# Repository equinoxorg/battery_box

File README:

#Battery Box 2013 Prototype

##Hardware
Hardware designs are made in eagle v6

##Software
Software is MPLAB IDE X v1.30 with the Hi Tech C Lite compiler

##Changes from 2012
Added Current Sense to prevent overcurrent failure
Changed uControoler to add no volatile memory
	Can be used to prevent over discharge and better batt level estimation
	Can be used as very simple datalogger, data can be exported through Serial Data out pins
Connectors have been added to board to reduce assembely time
Surface mount components used to reduce manufacture cost

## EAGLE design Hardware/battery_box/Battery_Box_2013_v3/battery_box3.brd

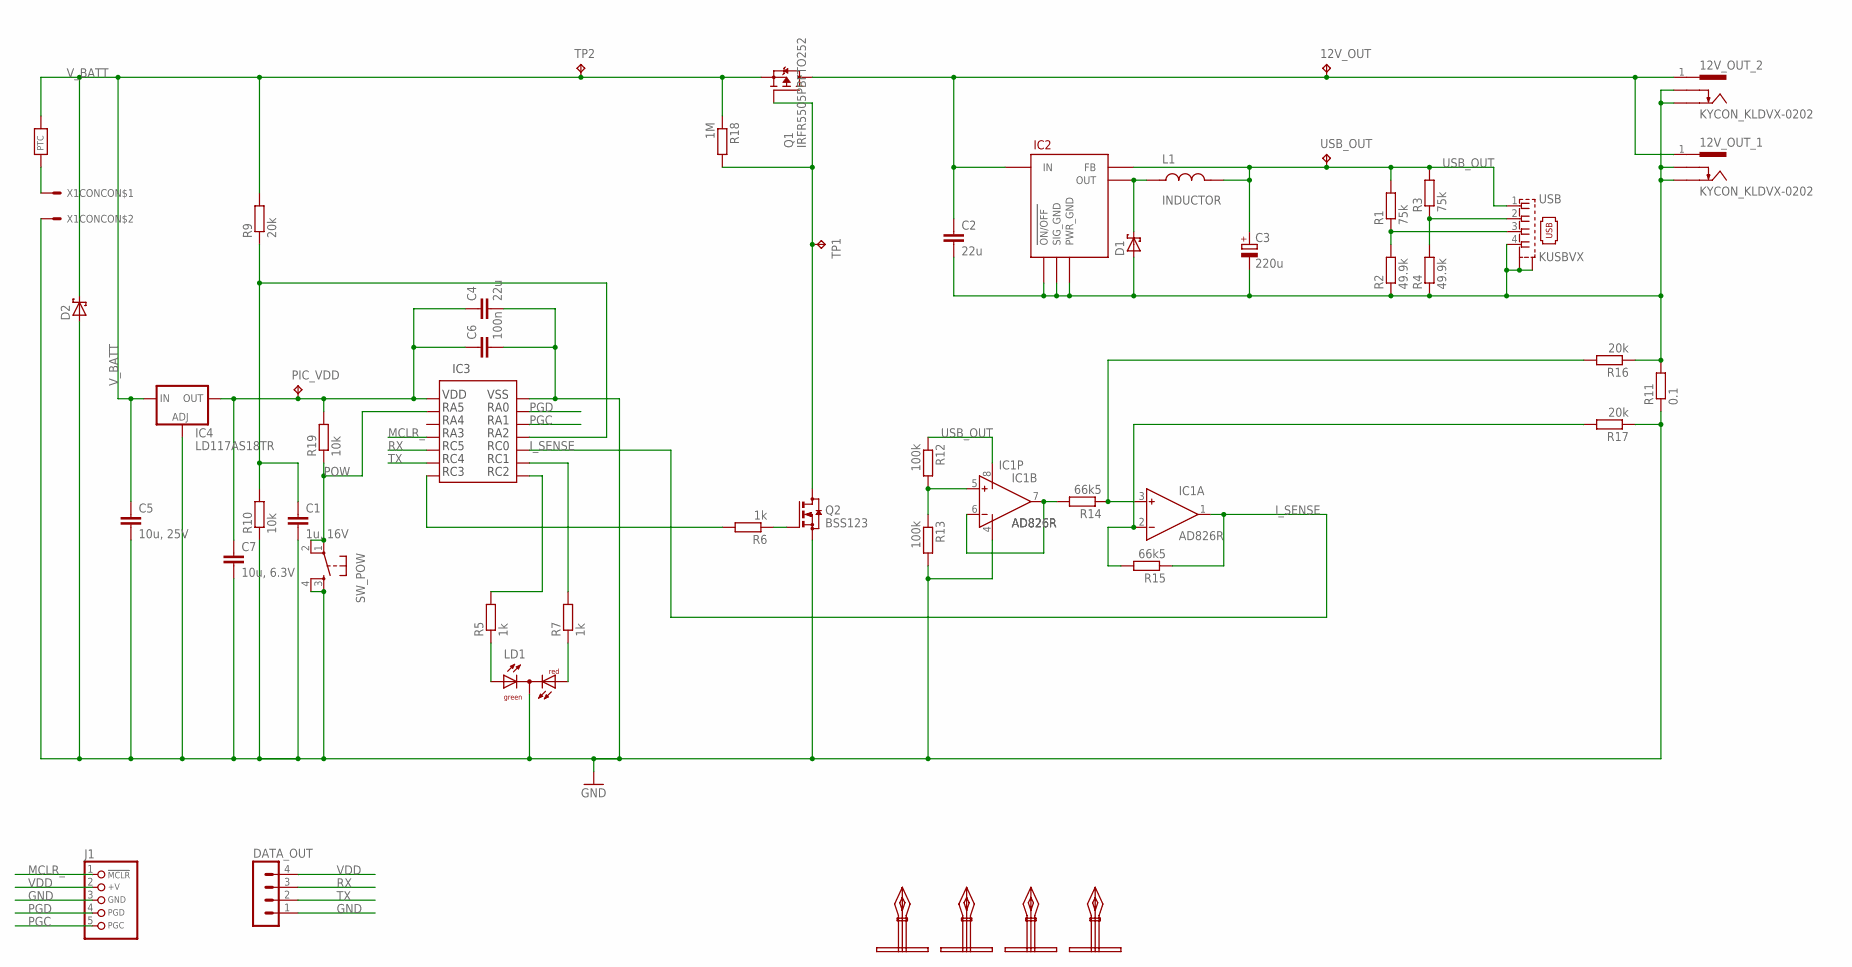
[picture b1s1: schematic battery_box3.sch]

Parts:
12V_OUT: TPTP20R; TP20R
12V_OUT_1, 12V_OUT_2: KYCON_KLDVX-0202; KYCON_KLVDX_2020_B
C1: 1u, 16V; C0805
C2: 22u; C1210
C3: 220u; PANASONIC_E
C4: 22u; C0805
C5: 10u, 25V; C1210
C6: 100n; C0402
C7: 10u, 6.3V; C0805
D1: SCHOTTKY-DIODESMD; SMB
D2: SCHOTTKY-DIODESMC; SMC
DATA_OUT: MA04-1
IC1: AD826R; SO8
IC2: LM2574; SO14W
IC3: PIC16F1824; SO-14
IC4: LD117AS18TR; SOT223
J1: CON_HEADER_PRG_PIC_ICSPA; HEADER_PRG_1X05
L1: INDUCTOR; SMD_INDUCTOR
LD1: DUOLED-RG-C; DUOLED-C-5MM
PIC_VDD: TPTP14R; TP14R
Q1: IRFR5505PBFTO252; TO252
Q2: BSS123; SOT23
R1, R3: 75k; R0805
R2, R4: 49.9k; R0805
R5, R6, R7: 1k; R0805
R9, R16, R17: 20k; R0805
R10, R19: 10k; R0805
R11: 0.1; R2512
R12, R13: 100k; R0805
R14, R15: 66k5; R0805
R18: 1M; R0805
SW_POW: TAC_SWITCHPTH; TACTILE-PTH
TP1: TPTP14R; TP14R
TP2: TPTP20R; TP20R
U$2: PTC; MINISMDC260F
U$5, U$6, U$7, U$8: PCB_MOUNT_RICHO; PCBMOUNT
USB: KUSBVX
USB_OUT: TPTP20R; TP20R
X1CON: CON_MOLEX_39_29_1028; MOLEX_39_29_1028

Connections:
12V_OUT: 12V_OUT.TP, 12V_OUT_1.1, 12V_OUT_2.1, C2.1, IC2.10 (IN), Q1.3 (D)
GND: C1.2, C4.2, C5.2, C6.2, C7.2, D2.A, DATA_OUT.1, IC1.4 (V-), IC3.14, IC4.1 (ADJ), J1.3 (GND), LD1.C, Q2.2 (S), R10.1, R11.1, R13.2, R17.1, SW_POW.3, SW_POW.4, X1CON.P$2
GND_OUTPUT: 12V_OUT_1.2, 12V_OUT_1.3, 12V_OUT_2.2, 12V_OUT_2.3, C2.2, C3.-, D1.A, IC2.4 (SIG_GND), IC2.5 (ON/OFF), IC2.6 (PWR_GND), R2.1, R4.1, R11.2, R16.1, USB.4, USB.M1 (S1), USB.M2 (S2)
I_SENSE: IC1.1 (OUT), IC3.10, R15.1
MCLR_: IC3.4, J1.1 (/MCLR)
unnamed: LD1.AR, R7.1
unnamed: R1.1, R2.2, USB.3
unnamed: LD1.AX (AG), R5.1
unnamed: R3.1, R4.2, USB.2
unnamed: U$2.P$1, X1CON.P$1
unnamed: IC3.9, R7.2
unnamed: C1.1, IC3.11, R9.1, R10.2
unnamed: D1.C, IC2.12 (OUT), L1.P$1
unnamed: IC3.8, R5.2
unnamed: Q1.1 (G), Q2.3 (D), R18.2, TP1.TP
unnamed: Q2.1 (G), R6.1
unnamed: IC3.7, R6.2
unnamed: IC1.3 (IN+), R14.1, R16.2
unnamed: IC1.2 (IN-), R15.2, R17.2
unnamed: IC1.5 (IN+), R12.2, R13.1
unnamed: IC1.6 (IN-), IC1.7 (OUT), R14.2
PGC: IC3.12, J1.5 (PGC)
PGD: IC3.13, J1.4 (PGD)
POW: IC3.2, R19.1, SW_POW.1, SW_POW.2
RX: DATA_OUT.3, IC3.5
TX: DATA_OUT.2, IC3.6
USB_OUT: C3.+, IC1.8 (V+), IC2.3 (FB), L1.P$2, R1.2, R3.2, R12.1, USB.1, USB_OUT.TP
VDD: C4.1, C6.1, C7.1, DATA_OUT.4, IC3.1, IC4.4 (OUT), J1.2 (+V), PIC_VDD.TP, R19.2
V_BATT: C5.1, D2.C, IC4.3 (IN), Q1.2 (S), R9.2, R18.1, TP2.TP, U$2.P$2

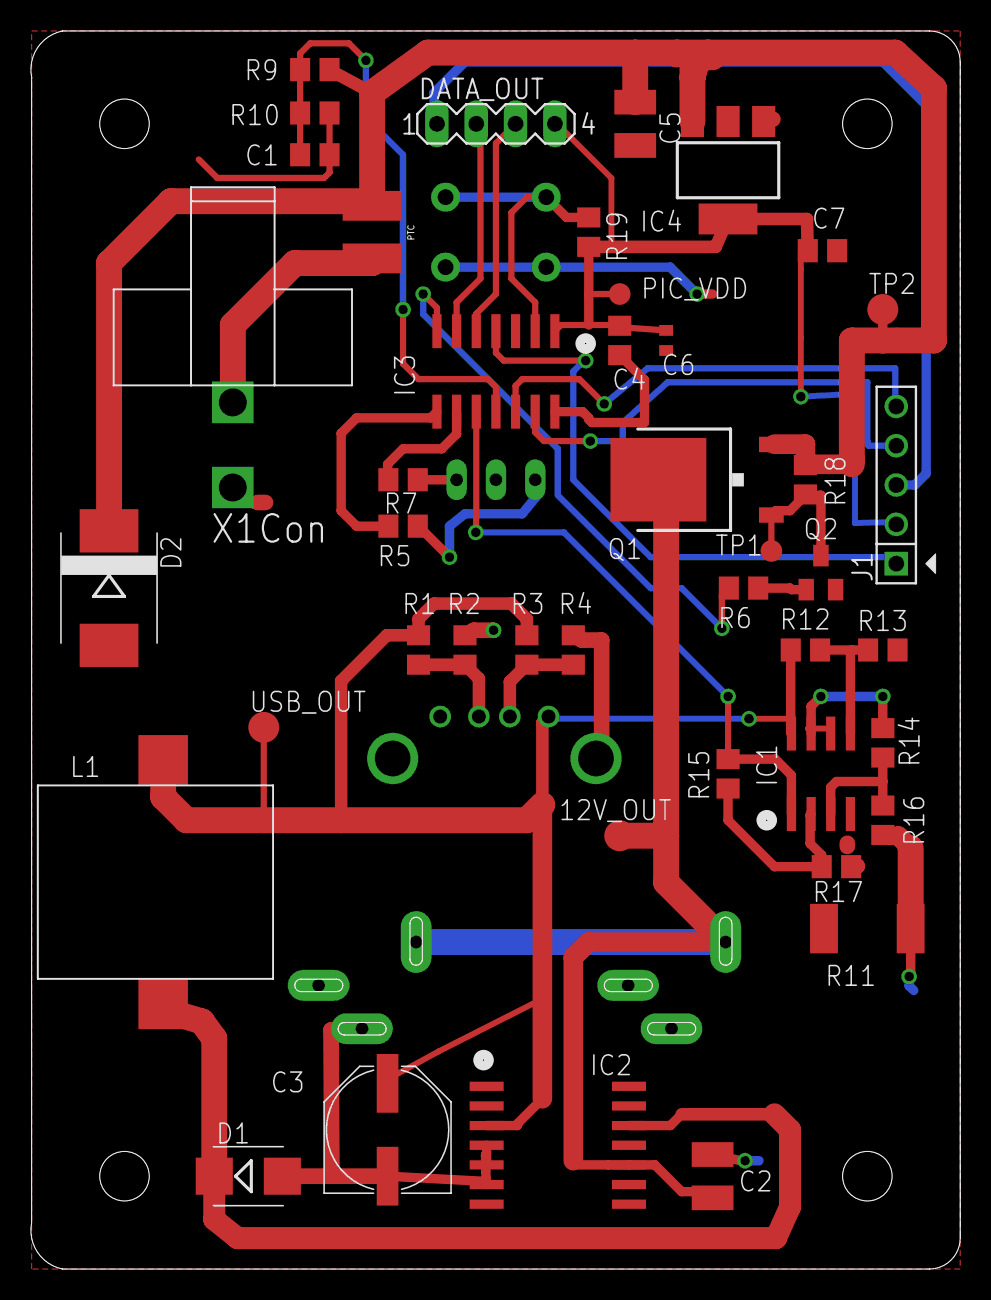
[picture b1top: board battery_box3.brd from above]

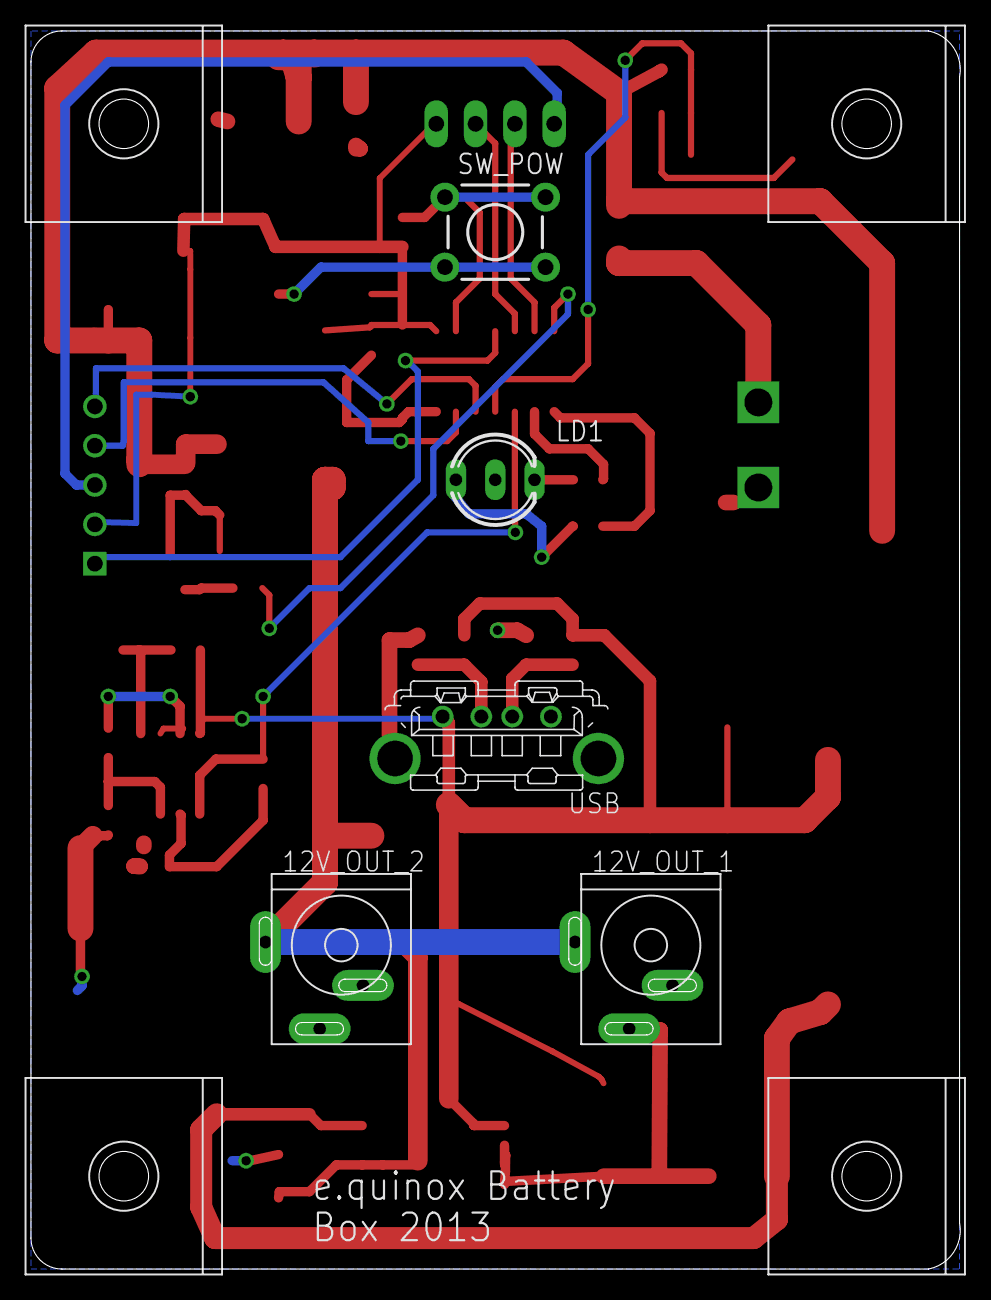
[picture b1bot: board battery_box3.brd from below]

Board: 2 copper layers, 60.0 x 80.0 mm, 52 parts (9 on the bottom side), 29 nets.

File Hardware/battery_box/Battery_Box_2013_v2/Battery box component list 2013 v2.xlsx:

|  | Battery Box component list 2013
Board label | Quantity | Function | Manufacturer | Manufacture name | Supplier | Order code | Quantity | Price | Total Cost | Comments | Current quantity
 | 2 | Crimp terminal for plug | MOLEX | 39-00-0213 | Onecall | 2063715 | 2 | 0.14000000000000001 | 0.28000000000000003
 | 1 | Receptacle connector | MOLEX | 39-01-2020 | Onecall | 151866 | 1 | 0.16800000000000001 | 0.16800000000000001
 | 1 | Battery Crimp red | Multicomp |  |  | 9971882 | 1 | 0.158 | 0.158 | could get cheaper 1339227, but test quality first
 | 1 | Battery Crimp blue | MULTICOMP |  |  | 9971904 | 1 | 0.14000000000000001 | 0.14000000000000001 | Could get cheaper 488331, but test quality first
 | 1 | LED Housing | KINGBRIGHT |  |  | 1105124 | 1 | 0.1 | 0.1
 |  | Cable
 |  | PCB
 |  | USBS |  |  |  | 1696536 | 1 | 0.26 | 0.26 |  | 200
 |  | Programmer header | TE CONNECTIVITY / AMP |  |  | 1248143 |  |  |  | NOT ACTUALLY NEEDED TE CONNECTIVITY / AMP - 826926-5 - HEADER, STRAIGHT, 5WAY | 180
 | 1 | LED |  |  |  | 2001770 | 1 | 0.13800000000000001 | 0.13800000000000001 |  | 200
 | 2 | DC Socket |  |  |  |  | 2 | 0.22 | 0.44 | price for 500+ | 200
 | 1 | Battery connector header | MOLEX | 39-29-1028 | Onecall | 1012166 | 1 | 0.41 | 0.41 |  | 200
SW_POW | 1 | Switch | TE CONNECTIVITY | FSM6JH | Onecall | 758-1979 | 1 | 7.5999999999999998E-2 | 7.5999999999999998E-2 |  | 200
 | 1 | Switch Cap | MULTICOMP |  |  | 9561552 | 1 | 2.7E-2 | 2.7E-2 | MULTICOMP - KTSC-22K - CAP, ROUND, BLACK | 200
PTC | 1 | PTC | TE CONNECTIVITY | MINISMDC260F | Onecall | 1345935 | 1 | 0.191 | 0.191 |  | 3
IC4 | 1 | 5V regulator | NXP | BZX384-C5V1 | Onecall | 2057286 | 1 | 2.1999999999999999E-2 | 2.1999999999999999E-2 |  | 200
IC3 | 1 | PIC microcontroller | MICROCHIP | PIC16F1824-I/SL | Onecall | 1814945 | 1 | 1.01 | 1.01 | 70p in bulk | 192
R9, R16, R17 | 3 | 20k resistor | MULTICOMP | MCSR08X2002FTL | Onecall | 2074395 | 3 | 8.9999999999999993E-3 | 2.6999999999999996E-2 |  | 92
R10, R19 | 2 | 10k resistor | MULTICOMP | MCSR08X1002FTL | Onecall | 2074334 | 2 | 8.9999999999999993E-3 | 1.7999999999999999E-2
R12, R13 | 2 | 100k Resistor | MULTICOMP | MCMR08X1003FTL | Onecall | 2073608 | 2 | 8.9999999999999993E-3 | 1.7999999999999999E-2 |  | 95
R1, R3 | 2 | 75k Resistor | MULTICOMP | MCMR08X7502FTL | Onecall | 2073840 | 2 | 8.9999999999999993E-3 | 1.7999999999999999E-2 |  | 95
R14, R15 | 2 | 66k5 Resistor | VISHAY |  |  | 2139016 | 2 | 6.0000000000000001E-3 | 1.2E-2 |  | 45
R2, R4 | 2 | 49.9k Resistor | PANASONIC |  |  | 2057651 | 2 | 1.7000000000000001E-2 | 3.4000000000000002E-2 |  | 45
R5, R6, R7 | 3 | 1k Resistor | MULTICOMP |  |  | 2073611 | 3 | 7.0000000000000001E-3 | 2.1000000000000001E-2 |  | 85
R18 | 1 | 1M Resistor | MULTICOMP |  |  | 2073615 | 1 | 7.0000000000000001E-3 | 7.0000000000000001E-3 |  | 98
R11 | 1 | 0.1 ohm resistor | BOURNS |  |  | 1865265 | 1 | 0.12 | 0.18 |  | 209
C1 | 1 | 1u capacitor | MULTICOMP |  |  | CA06731 | 1 | 0.01 | 0.01 |  | 99
C4 | 1 | 22u capacitor, 6.3v | MULTICOMP |  |  | CA06719 | 1 | 0.08 | 0.08 |  | 90
C2 | 1 | 22u capacitor, 16V | MULTICOMP |  |  | CA06789 | 1 | 0.23400000000000001 | 0.23400000000000001 |  | 200
C3 | 1 | 220u capacitor, 6.3V | PANASONIC |  |  | 9694340 | 1 | 0.35 | 0.35
IC2 | 1 | 12-5V Regulator | TEXAS INSTRUMENTS | LM2574M-5.0 | Onecall | SC10367 | 1 | 0.63 | 0.63 |  | 193
L1 | 1 | Inductor | MULTICOMP | MCBFS7330-331MU | Onecall | 1864293 | 1 | 0.28000000000000003 | 0.28000000000000003 |  | 193
Q1 | 1 | P-MOS Power MOSFET | International Rectifier | IRFR5505PBF | Onecall | 8649839 | 1 | 0.32 | 0.32 |  | 203
Q2 | 1 | N-MOS Signal MOSFET | NXP | NX7002AKW | Onecall | 2191748 | 1 | 3.1E-2 | 3.1E-2 |  | 202
IC1 | 1 | Operational Amplifier | TEXAS INSTRUMENTS | TL103WID | Onecall | 1755223 | 1 | 0.25 | 0.25 |  | 203
C5 | 1 | 10u Capacitor | MULTICOMP |  |  | 1759470 | 1 | 0.26 | 0.26 |  |  | 5
D2, D3 | 2 | Schottky Diode 40V output | MULTICOMP |  |  | 1861427 | 2 | 0.121 | 0.24199999999999999 | Could be cheaper? | 400 | 5
D1 | 1 | Schottky Diode 20V output | MULTICOMP |  |  | 1861424 | 1 | 0.05 | 0.05 |  | 200 | 5
C6 | 1 | 0.1u Capacitor | AVX |  |  | 1327657 | 1 | 3.3000000000000002E-2 | 3.3000000000000002E-2 | Could get cheaper in smaller package, but didn’t have time to redesign board |  | 5
C8 | 1 | 10u Capacitor | TDK |  |  | 2309029 | 1 | 2.8000000000000001E-2 | 2.8000000000000001E-2 |  |  | 5
 |  |  |  |  |  |  |  |  | 6.552999999999999

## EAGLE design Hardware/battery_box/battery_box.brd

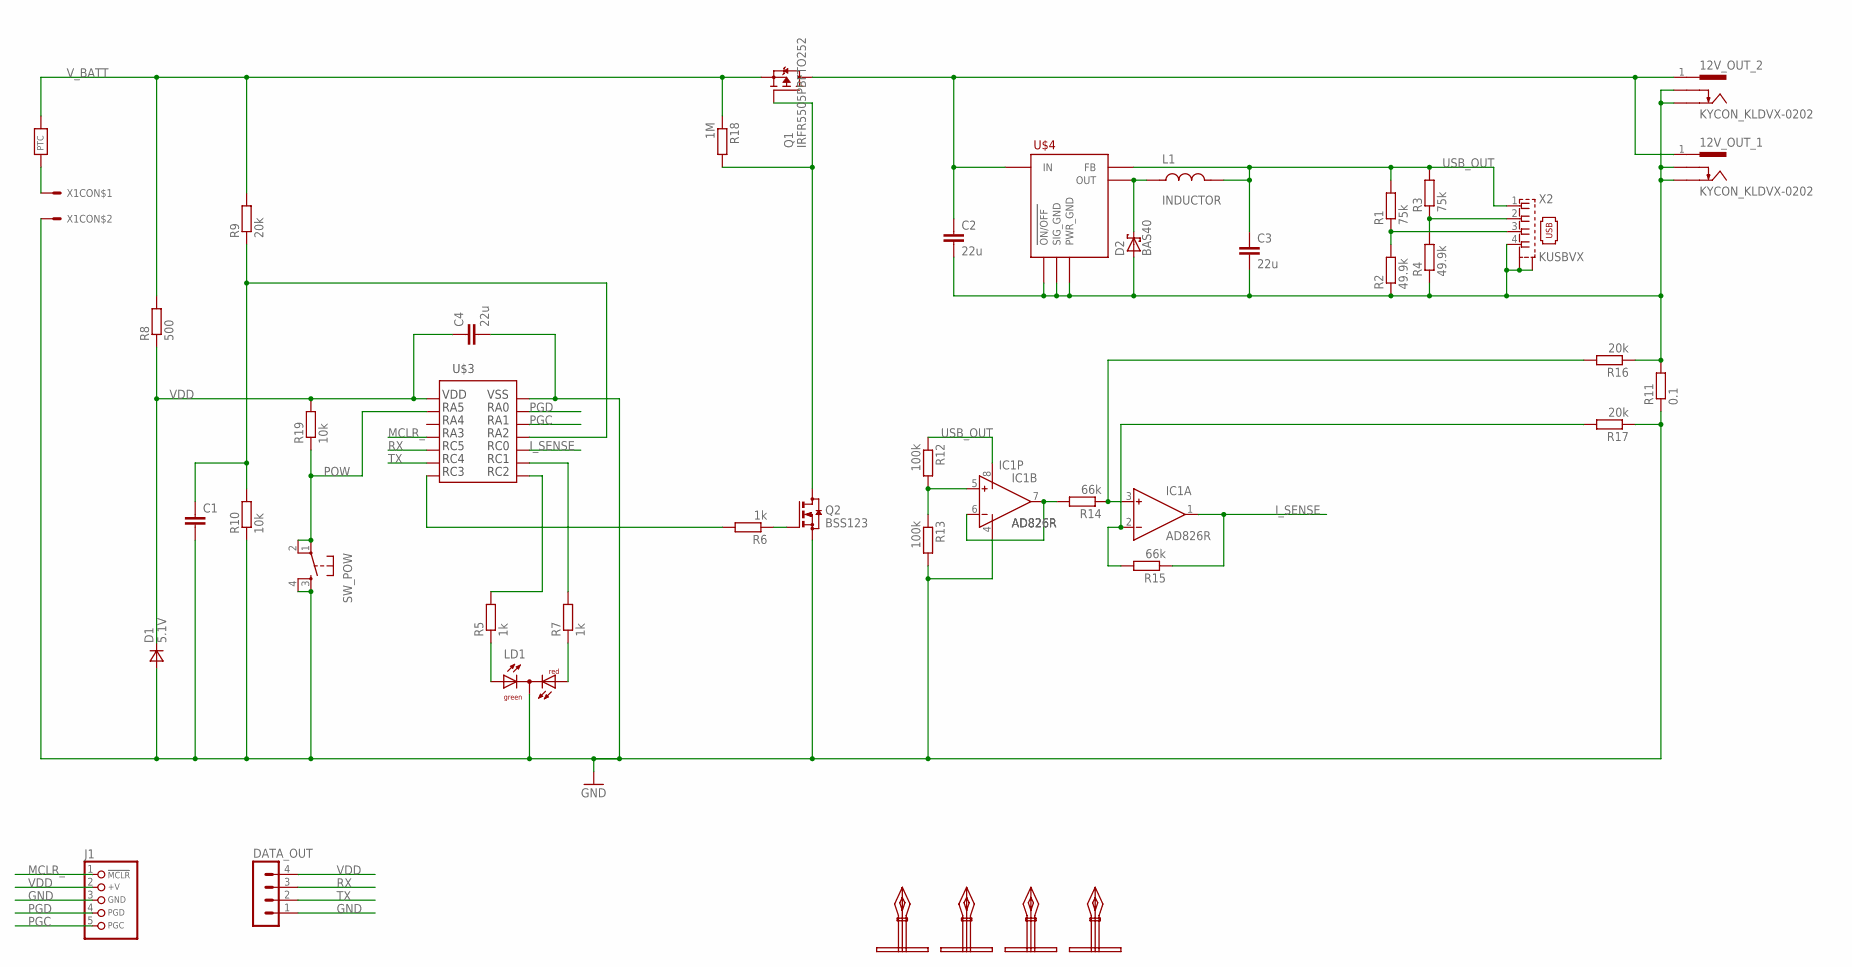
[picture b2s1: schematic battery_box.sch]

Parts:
12V_OUT_1, 12V_OUT_2: KYCON_KLDVX-0202; KYCON_KLVDX_2020_B
C1: C-EUC0805; C0805
C2, C3, C4: 22u; C0805
D1: 5.1V; SOD323
D2: BAS40; SOT23
DATA_OUT: MA04-1
IC1: AD826R; SO8
J1: CON_HEADER_PRG_PIC_ICSPA; HEADER_PRG_1X05
L1: INDUCTOR; SMD_INDUCTOR
LD1: DUOLED-RG-C; DUOLED-C-5MM
Q1: IRFR5505PBFTO252; TO252
Q2: BSS123; SOT23
R1, R3: 75k; R0805
R2, R4: 49.9k; R0805
R5, R6, R7: 1k; R0805
R8: 500; R0805
R9, R16, R17: 20k; R0805
R10, R19: 10k; R0805
R11: 0.1; R2512
R12, R13: 100k; R0805
R14, R15: 66k; R0805
R18: 1M; R0805
SW_POW: TAC_SWITCHPTH; TACTILE-PTH
U$1: EQUINOX_LOGO_SMALL
U$2: PTC; MINISMDC260F
U$3: PIC16F1824; SO-14
U$4: LM2574; SO14W
U$5, U$6, U$7, U$8: PCB_MOUNT_RICHO; PCBMOUNT
X1: CON_MOLEX_39_29_1028; MOLEX_39_29_1028
X2: KUSBVX

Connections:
GND: C1.2, C4.2, D1.2 (A), DATA_OUT.1, IC1.4 (V-), J1.3 (GND), LD1.C, Q2.2 (S), R10.1, R11.1, R13.2, R17.1, SW_POW.3, SW_POW.4, U$3.14, X1.P$2
I_SENSE: IC1.1 (OUT), R15.1, U$3.10
MCLR_: J1.1 (/MCLR), U$3.4
unnamed: 12V_OUT_1.1, 12V_OUT_2.1, C2.1, Q1.3 (D), U$4.10 (IN)
unnamed: LD1.AR, R7.1
unnamed: R1.1, R2.2, X2.3
unnamed: LD1.AX (AG), R5.1
unnamed: R3.1, R4.2, X2.2
unnamed: U$2.P$1, X1.P$1
unnamed: R7.2, U$3.9
unnamed: C1.1, R9.1, R10.2, U$3.11
unnamed: D2.3 (C), L1.P$1, U$4.12 (OUT)
unnamed: R5.2, U$3.8
unnamed: Q1.1 (G), Q2.3 (D), R18.2
unnamed: Q2.1 (G), R6.1
unnamed: R6.2, U$3.7
unnamed: IC1.3 (IN+), R14.1, R16.2
unnamed: IC1.2 (IN-), R15.2, R17.2
unnamed: IC1.5 (IN+), R12.2, R13.1
unnamed: IC1.6 (IN-), IC1.7 (OUT), R14.2
unnamed: 12V_OUT_1.2, 12V_OUT_1.3, 12V_OUT_2.2, 12V_OUT_2.3, C2.2, C3.2, D2.1 (A), R2.1, R4.1, R11.2, R16.1, U$4.4 (SIG_GND), U$4.5 (ON/OFF), U$4.6 (PWR_GND), X2.4, X2.M1 (S1), X2.M2 (S2)
PGC: J1.5 (PGC), U$3.12
PGD: J1.4 (PGD), U$3.13
POW: R19.1, SW_POW.1, SW_POW.2, U$3.2
RX: DATA_OUT.3, U$3.5
TX: DATA_OUT.2, U$3.6
USB_OUT: C3.1, IC1.8 (V+), L1.P$2, R1.2, R3.2, R12.1, U$4.3 (FB), X2.1
VDD: C4.1, D1.1 (C), DATA_OUT.4, J1.2 (+V), R8.1, R19.2, U$3.1
V_BATT: Q1.2 (S), R8.2, R9.2, R18.1, U$2.P$2

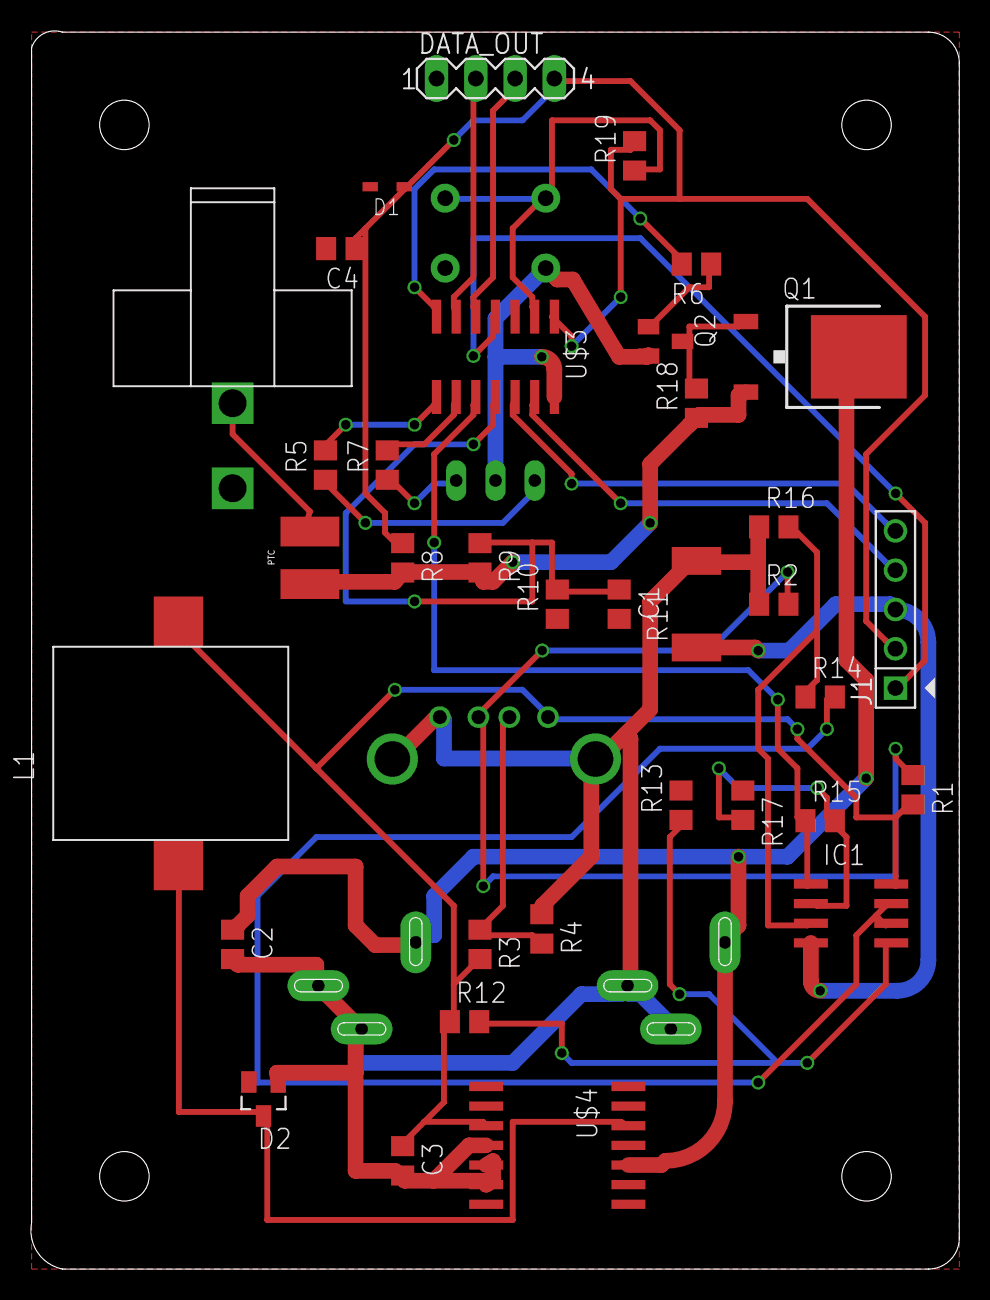
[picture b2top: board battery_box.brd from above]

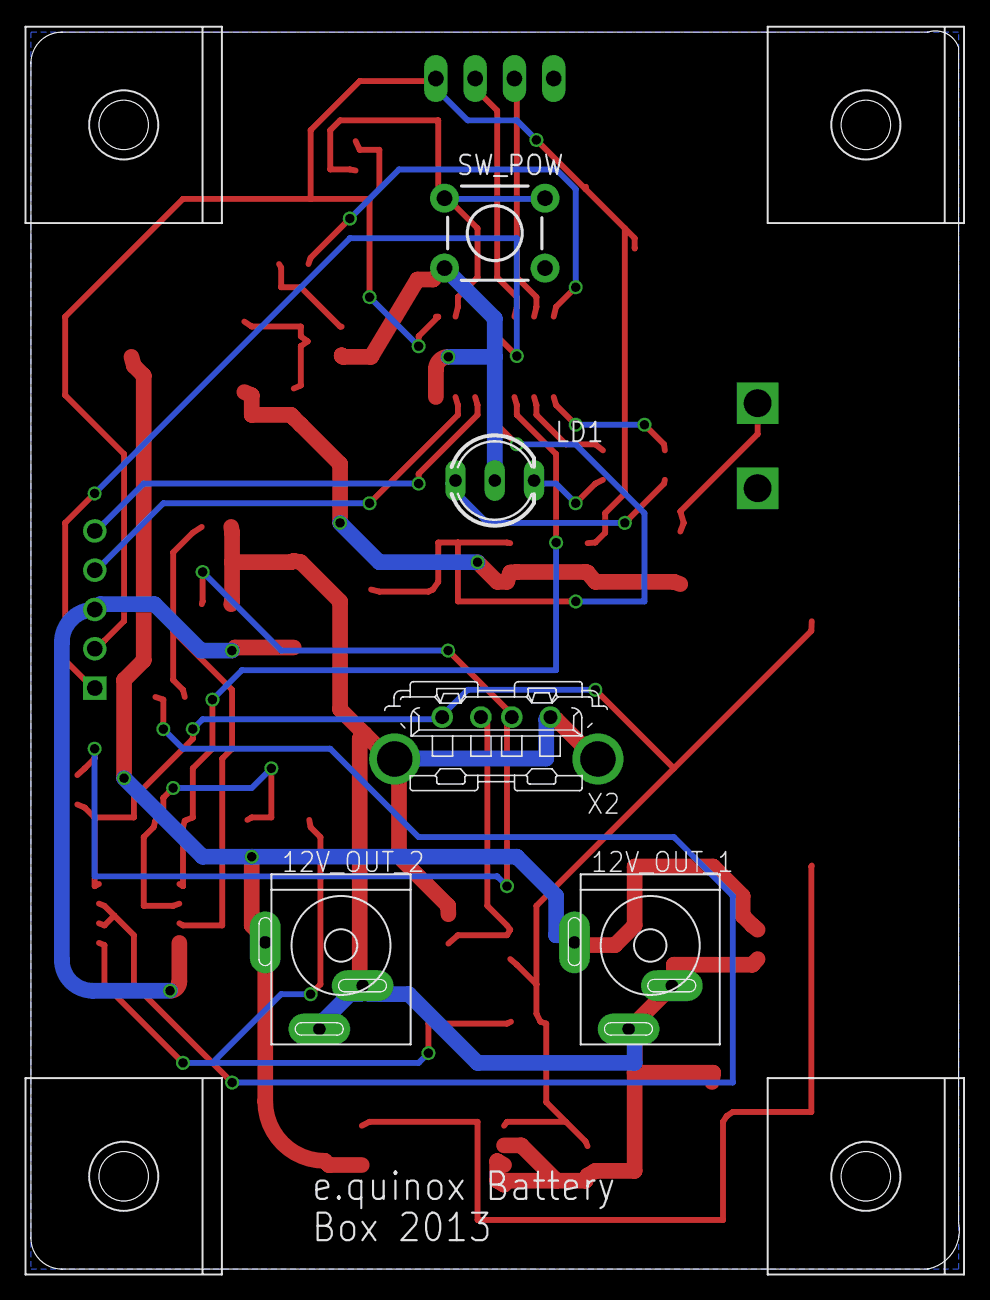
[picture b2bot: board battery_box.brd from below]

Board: 2 copper layers, 60.0 x 80.1 mm, 45 parts (10 on the bottom side), 29 nets.

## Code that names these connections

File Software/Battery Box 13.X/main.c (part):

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 |
 |                   __________
 |	VCC         |1      14| GND
 |(RA5) POW_SW      |2      13| PGD     (Programming Pin)
 |                  |3      12| PGC     (Programming Pin)
 |      ~MCLR       |4      11| BATT_V (Stepdown to 0-5V)   (RA2/AN2)
 |(RC5)	RX          |5      10| I_SENSE                     (RC0/AN4)
 |(RC4)	TX          |6       9| RED LED     RC1
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#define LVCO_PIN	(1 << 3)    //RC3
#define LEDR_PIN	(1 << 1)    //RC1
#define LEDG_PIN	(1 << 2)    //RC2
#define I_SENSE_PIN     (1 << 0)

//Analogue input pins
#define BATT_V	2
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
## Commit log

2012-10-23 First Upload
    This is the hardware and software designs used for the 2012 battery box
    deployment at the hydro site.
2012-11-14 Add license information
2012-11-14 Changed licence
2012-12-05 Add Improvments File
2012-12-05 Added Connectors to Schematic
    Adds the DC Jacks and USB connectors and LEDs to the schematic for
    mounting on PCB. Added comments to schematic and changed .gitignore
2013-01-11 Added cooments to fix problems identified
    Problems identified during 2013 Jan trip have added as comments.
2013-02-27 Added the Connector Test PCB
2013-02-27 Added equinox lib
2013-02-27 Version 0.1 of PIC16F1824 code
    Just turns some LEDs on and off at the moment.
2013-03-20 Electronics added.
    Should be first fully working prototype of 2013 unit. See README for
    changes from 2012 version.
2013-03-20 Added comments to Schematic
2013-03-21 Changed location op a mp power supply
2013-03-30 Added Latest Gerbers
2013-03-30 Possible fix for ADC reading issues.
2013-04-09 Fixed ADC Read Function
    Mistake in combine low and high bits. Was ANDing two together when
    should OR. ANDing will clear all bits.
2013-04-13 ADC Works. Added I_SENSE code
    - Added current sense code as well as voltage measurement
2013-04-20 Code for writing to eeprom *untested*
    Need to implement the sleep routine
2013-04-20 Code for writing to eeprom *untested*
    Added a line to set up ADC in bank C for I_Sense
    Still need to implement interrupts
2013-04-20 Added interrupt-on-change functionality for POW. *untested*
    Puts chip to sleep. Still untested.
2013-04-26 First PCB Layout
2013-04-27 EEPROM code fully tested and working
    Contains some minor fixes
2013-05-06 EEPROM code modified to work with PCB (in progress)
    Still in the process of testing
2013-05-10 Code modified to only cut off and turn back on
    All new features disabled.
2013-05-17 Updated the DC Jack and Battery Connector
    Fixed problems with footprints
2013-05-17 Changed Current Sense Resistor Values
2013-05-17 Corrected the Readme file extension.
2013-05-30 Added CAM Files
    Seeed Studio and EEE Cam files
2013-06-02 Fixed addressing of EEPROM
2013-06-02 Fixed LED Pin Macros
2013-06-02 Fixed Interrupt Code
    IOCAP |= 1 << 5; line was wrong, was previously setting up interrupt on
    in 4
2013-06-04 Cleaned up and many code fixes
    Code fixes include:
    -Preset voltage levels for cutout was calculated for 8-bit ADC. Now
    correct for 10-bit ADC
    -Some Initilisation fixes
    - State machine ensures output pins are correct on each iteration
2013-06-11 Updated PDFs with latest designs
2013-06-20 Working code
    Might be some bugs if battery voltage is between charging voltage and LV
    disconnect voltage. More testing is needed.
2013-06-21 Light now no longer flickers when on
    It still flickers when voltage is low, but above cut off. This isn't a problem if we don't turn on red and green LED at the same time.
    Another problem: Light doesn't turn on when voltage is above cut off voltage, but below the charging voltage.
2013-06-21 Cleaned up the code a bit more from the previous edit
2013-06-22 Attempted to make changes as discussed
    Changes left in complete routing.
    Sorted out the labels and added in diodes across the terminals and
    MOSFET, the Vreg with its caps and another decoupling cap for the PIC.
    See email for questions.
2013-06-22 Cleaned up and routed PCB and Schematic files
2013-06-23 Added new components with correct footprints
2013-06-24 Re-routed PCB
2013-06-25 Separated new and old PCB versions. Added Gerbers
2013-06-25 Fixed the flickering
2013-06-30 added pdf of schematic
2013-06-30 Board PDF
2013-07-01 updated C3 footprint and component values/cost
2013-07-05 Added Mechanical Faceplate Designs
2013-07-07 Most recent Gerbers
    Most recent footprints and testpoints added.
2013-09-01 Current sense now working
2013-09-05 Feature complete code (first release)
    *Requires more testing*
    Features:
    - LVDC
    - Low charge indication
    - Charging indication (box needs to be powered on for this to work)
    - Charging complete indication
2013-09-07 Feature complete code (release 2)
    Contains minor bug fixes:
    - Charged indication flickers less (increased current threshold)
    - Tweaked the over current protection. Limit is now 800mA.
2013-09-21 Feature complete code (release 3)
    Reduced the charging voltage to 12.3V
2013-11-06 Added Battery Box V3
2013-11-11 Battery box faceplate pdf added
2013-11-11 Code copy
    No changes made
2013-11-11 Same commit

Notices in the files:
Software/Battery Box 13.X/main.c:
Copyright (C) 2013  Ashley Grealish & Yuchen Wang - www.e.quinox.org
This program is free software: you can redistribute it and/or modify
it under the terms of the GNU General Public License as published by
the Free Software Foundation, either version 3 of the License, or
(at your option) any later version.
parts and their libraries:
SparkFun: Licensing: CC v3.0 Share-Alike You are welcome to use this library for commercial purposes.
